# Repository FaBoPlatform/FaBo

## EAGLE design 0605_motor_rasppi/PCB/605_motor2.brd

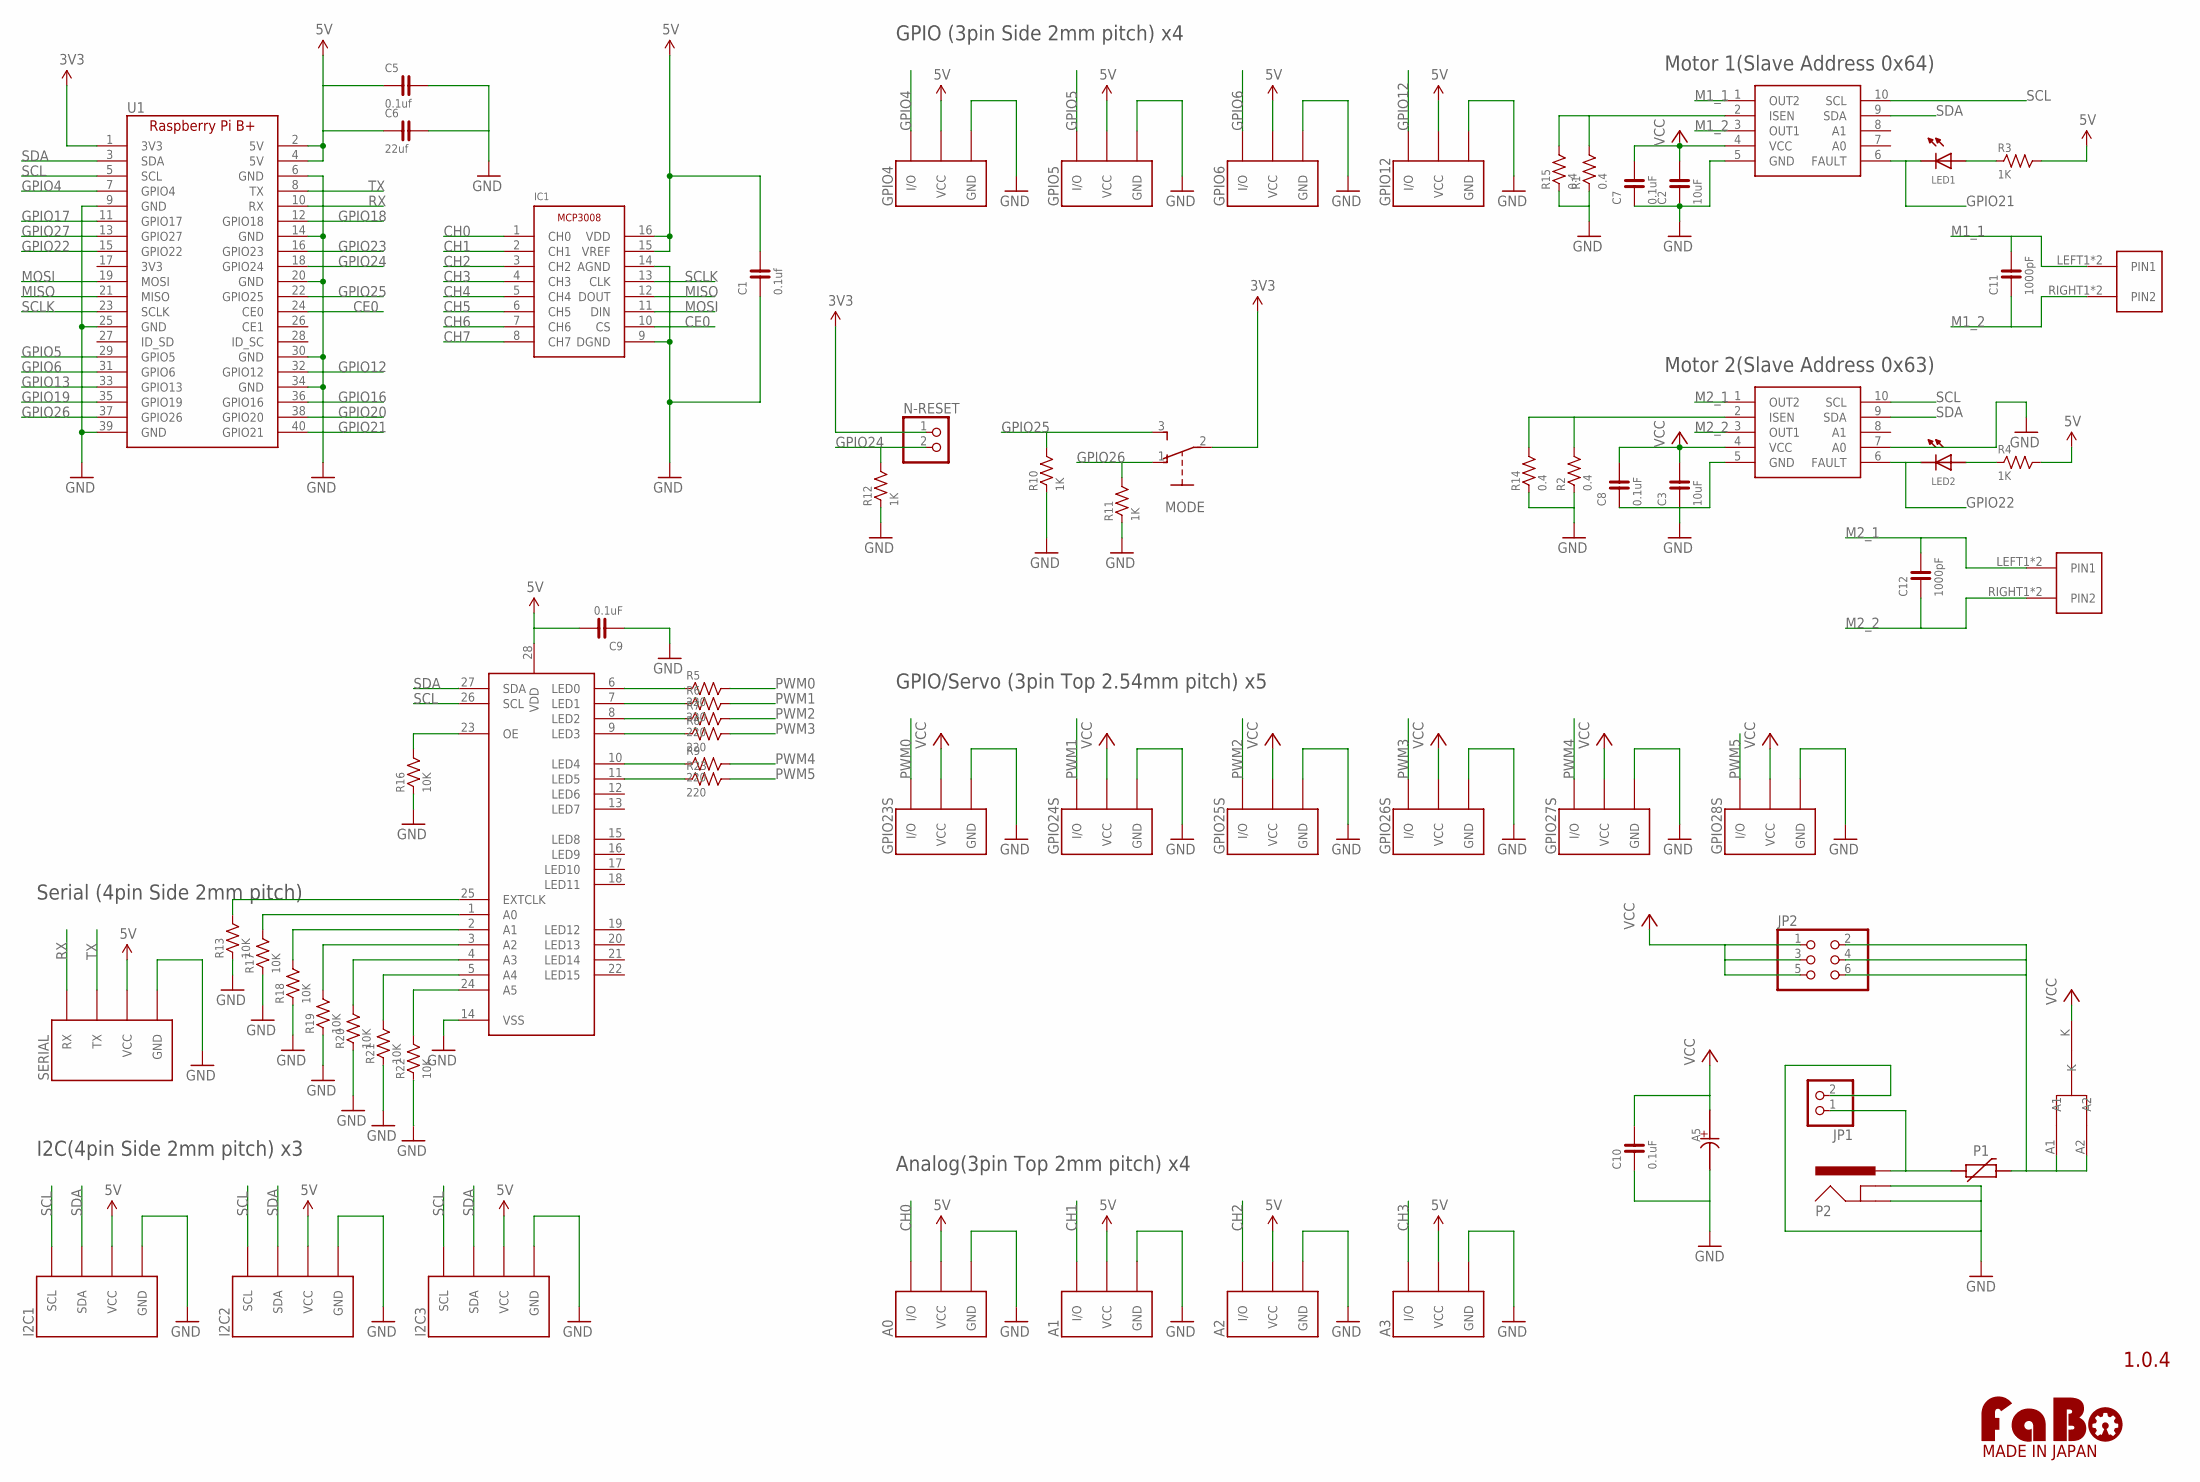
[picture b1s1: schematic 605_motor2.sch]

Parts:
A0, A1, A2, A3: FABO_BRICK_3PIN-B03B-PASK-1; FABO_BRICK_3PIN_B03B-PASK-1
A5: CAPACITOR-ALUMIN_D12_5; D12.5
C1, C5: 0.1uf; 0603
C2, C3: 10uF; 0603
C6: 22uf; 0603
C7, C8, C9, C10: 0.1uF; 0603
C11, C12: 1000pF; 0603
GPIO4, GPIO5, GPIO6, GPIO12: FABO_BRICK_3PIN-S03B-PASK-2; FABO_BRICK_3PIN_S03B-PASK-2
GPIO23S, GPIO24S, GPIO25S, GPIO26S, GPIO27S, GPIO28S: FABO_BRICK_3PIN-HEADER; FABO_BRICK_3PIN_HEADER
I2C1, I2C2, I2C3: FABO_BRICK_I2C-S04B-PASK-2; FABO_BRICK_I2C_S04B-PASK-2
IC1: MICROCHIP-MCP3008
JP1: PINHD-1X2; 1X02
JP2: PINHD-2X3; 2X03
LED1, LED2: LED-0603; 0603
MODE: SLIDE-EG1218; EG1218
N-RESET: PINHD-1X2; 1X02
P1: POLYSWITCH1206; 1206
P2: DC-JACKM04339A0; M04339A0
R1, R2, R14, R15: 0.4; 0603
R3, R4, R10, R11, R12: 1K; 0603
R5, R6, R7, R8, R9, R23: 220; 0603
R13, R22: 10K; 0402
R16, R17, R18, R19, R20, R21: 10K; 0603
S1: STPS15L30C
SERIAL: FABO_BRICK_SERIAL-S04B-PASK-2; FABO_BRICK_SERIAL_S04B-PASK-2
U1: RASPBERRY_PI_B+
U$8, U$10: DRV8830
U$9: PCA9685
U$12, U$13: ML-1400-S1
U$14: LOGO_FABO-M; LOGO_FABO_MS

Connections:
3V3: MODE.2, N-RESET.1, U1.1 (3V3)
5V: A0.VCC, A1.VCC, A2.VCC, A3.VCC, C1.2, C5.1, C6.1, C9.2, GPIO4.VCC, GPIO5.VCC, GPIO6.VCC, GPIO12.VCC, I2C1.VCC, I2C2.VCC, I2C3.VCC, IC1.15 (VREF), IC1.16 (VDD), R3.2, R4.2, SERIAL.VCC, U1.2 (5V), U1.4 (5V), U$9.28 (VDD)
CE0: IC1.10 (CS), U1.24 (CE0)
CH0: A0.I/O, IC1.1 (CH0)
CH1: A1.I/O, IC1.2 (CH1)
CH2: A2.I/O, IC1.3 (CH2)
CH3: A3.I/O, IC1.4 (CH3)
CH4: IC1.5 (CH4)
CH5: IC1.6 (CH5)
CH6: IC1.7 (CH6)
CH7: IC1.8 (CH7)
GND: A0.GND, A1.GND, A2.GND, A3.GND, A5.-, C1.1, C2.1, C3.1, C5.2, C6.2, C7.1, C8.1, C9.1, C10.1, GPIO4.GND, GPIO5.GND, GPIO6.GND, GPIO12.GND, GPIO23S.GND, GPIO24S.GND, GPIO25S.GND, GPIO26S.GND, GPIO27S.GND, GPIO28S.GND, I2C1.GND, I2C2.GND, I2C3.GND, IC1.9 (DGND), IC1.14 (AGND), JP1.2, P2.GND@2 (GND), P2.GND@3 (GNDBREAK), R1.1, R2.1, R10.1, R11.1, R12.1, R13.P$1 (1), R14.1, R15.1, R16.1, R17.1, R18.1, R19.1, R20.1, R21.1, R22.P$1 (1), SERIAL.GND, U1.6 (GND), U1.9 (GND), U1.14 (GND), U1.20 (GND), U1.25 (GND), U1.30 (GND), U1.34 (GND), U1.39 (GND), U$8.5 (GND), U$9.14 (VSS), U$10.5 (GND), U$10.7 (A0)
GPIO4: GPIO4.I/O, U1.7 (GPIO4)
GPIO5: GPIO5.I/O, U1.29 (GPIO5)
GPIO6: GPIO6.I/O, U1.31 (GPIO6)
GPIO12: GPIO12.I/O, U1.32 (GPIO12)
GPIO13: U1.33 (GPIO13)
GPIO16: U1.36 (GPIO16)
GPIO17: U1.11 (GPIO17)
GPIO18: U1.12 (GPIO18)
GPIO19: U1.35 (GPIO19)
GPIO20: U1.38 (GPIO20)
GPIO21: LED1.CATHODE, U1.40 (GPIO21), U$8.6 (FAULT)
GPIO22: LED2.CATHODE, U1.15 (GPIO22), U$10.6 (FAULT)
GPIO23: U1.16 (GPIO23)
GPIO24: N-RESET.2, R12.2, U1.18 (GPIO24)
GPIO25: MODE.3, R10.2, U1.22 (GPIO25)
GPIO26: MODE.1, R11.2, U1.37 (GPIO26)
GPIO27: U1.13 (GPIO27)
LED0: R5.1, U$9.6 (LED0)
LED1: R6.1, U$9.7 (LED1)
LED2: R7.1, U$9.8 (LED2)
LED3: R8.1, U$9.9 (LED3)
LED4: R9.1, U$9.10 (LED4)
LED5: R23.1, U$9.11 (LED5)
M1_1: C11.2, U$8.1 (OUT2), U$12.LEFT1 (PIN1), U$12.LEFT2 (PIN1)
M1_2: C11.1, U$8.3 (OUT1), U$12.RIGHT1 (PIN2), U$12.RIGHT2 (PIN2)
M2_1: C12.2, U$10.1 (OUT2), U$13.LEFT1 (PIN1), U$13.LEFT2 (PIN1)
M2_2: C12.1, U$10.3 (OUT1), U$13.RIGHT1 (PIN2), U$13.RIGHT2 (PIN2)
MISO: IC1.12 (DOUT), U1.21 (MISO)
MOSI: IC1.11 (DIN), U1.19 (MOSI)
unnamed: R1.2, R15.2, U$8.2 (ISEN)
unnamed: R2.2, R14.2, U$10.2 (ISEN)
unnamed: LED1.ANODE, R3.1
unnamed: JP1.1, P1.P$1 (1), P2.VCC (PWR)
unnamed: LED2.ANODE, R4.1
unnamed: R16.2, U$9.23 (OE)
unnamed: R13.P$2 (2), U$9.25 (EXTCLK)
unnamed: R17.2, U$9.1 (A0)
unnamed: R18.2, U$9.2 (A1)
unnamed: R19.2, U$9.3 (A2)
unnamed: R20.2, U$9.4 (A3)
unnamed: R21.2, U$9.5 (A4)
unnamed: R22.P$2 (2), U$9.24 (A5)
unnamed: JP2.2, JP2.4, JP2.6, P1.P$2 (2), S1.A1, S1.A2
PWM0: GPIO23S.I/O, R5.2
PWM1: GPIO24S.I/O, R6.2
PWM2: GPIO25S.I/O, R7.2
PWM3: GPIO26S.I/O, R8.2
PWM4: GPIO27S.I/O, R9.2
PWM5: GPIO28S.I/O, R23.2
RX: SERIAL.RX, U1.10 (RX)
SCL: I2C1.SCL, I2C2.SCL, I2C3.SCL, U1.5 (SCL), U$8.10 (SCL), U$9.26 (SCL), U$10.10 (SCL)
SCLK: IC1.13 (CLK), U1.23 (SCLK)
SDA: I2C1.SDA, I2C2.SDA, I2C3.SDA, U1.3 (SDA), U$8.9 (SDA), U$9.27 (SDA), U$10.9 (SDA)
TX: SERIAL.TX, U1.8 (TX)
VCC: A5.+, C2.2, C3.2, C7.2, C8.2, C10.2, GPIO23S.VCC, GPIO24S.VCC, GPIO25S.VCC, GPIO26S.VCC, GPIO27S.VCC, GPIO28S.VCC, JP2.1, JP2.3, JP2.5, S1.K, U$8.4 (VCC), U$10.4 (VCC)

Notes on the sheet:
1.0.4
GPIO (3pin Side 2mm pitch) x4
I2C(4pin Side 2mm pitch) x3
Serial (4pin Side 2mm pitch)
GPIO/Servo (3pin Top 2.54mm pitch) x5
Analog(3pin Top 2mm pitch) x4
Motor 1(Slave Address 0x64)
Motor 2(Slave Address 0x63)

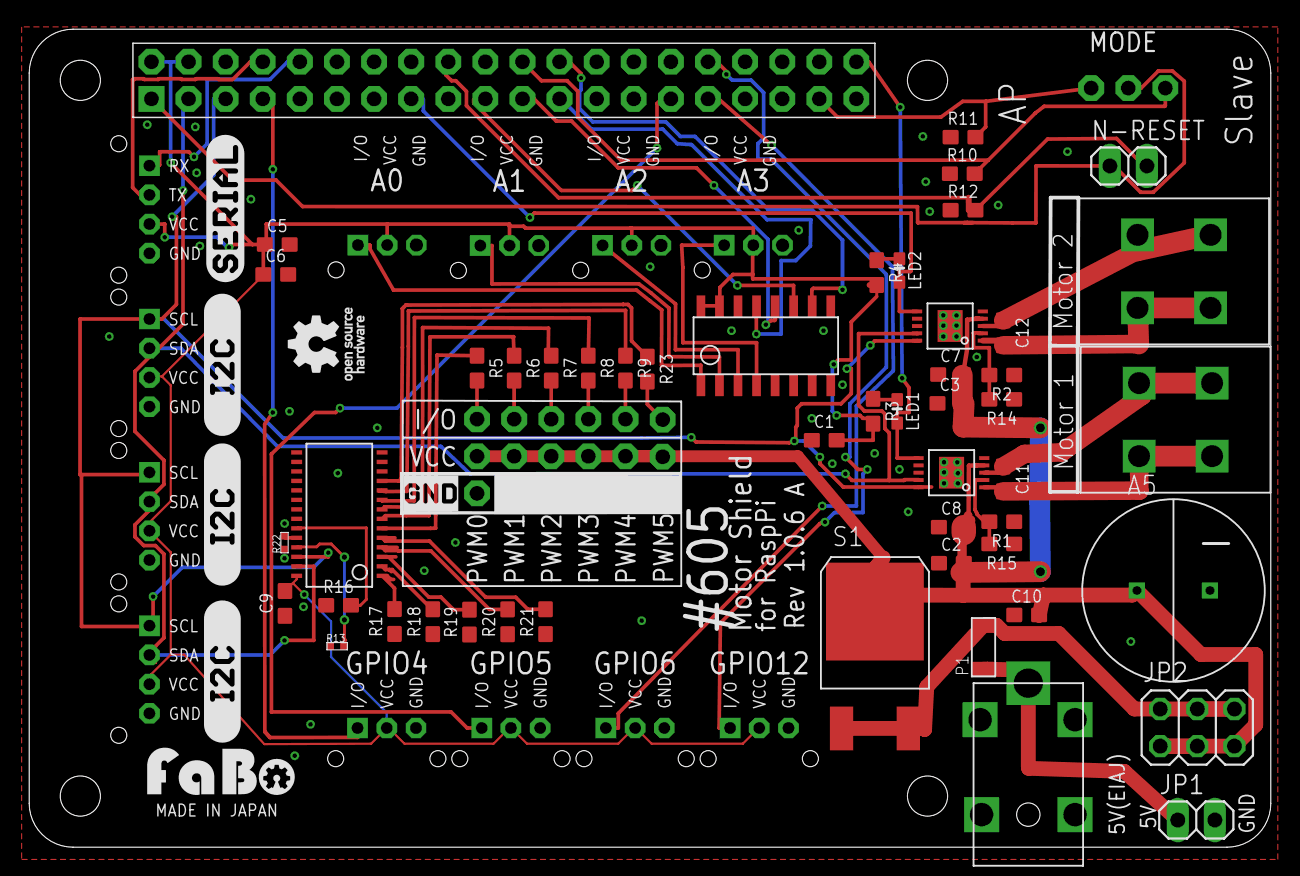
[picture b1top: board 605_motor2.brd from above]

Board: 2 copper layers, 85.0 x 56.0 mm, 76 parts (0 on the bottom side), 55 nets.

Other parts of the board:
U$2, U$5, U$6: LOGO_SILK_I2C
U$3: LOGO_SILK_SERIAL2
U$4: LOGO_OSHW_T_MS
U$7: LOGO_SILK_GND

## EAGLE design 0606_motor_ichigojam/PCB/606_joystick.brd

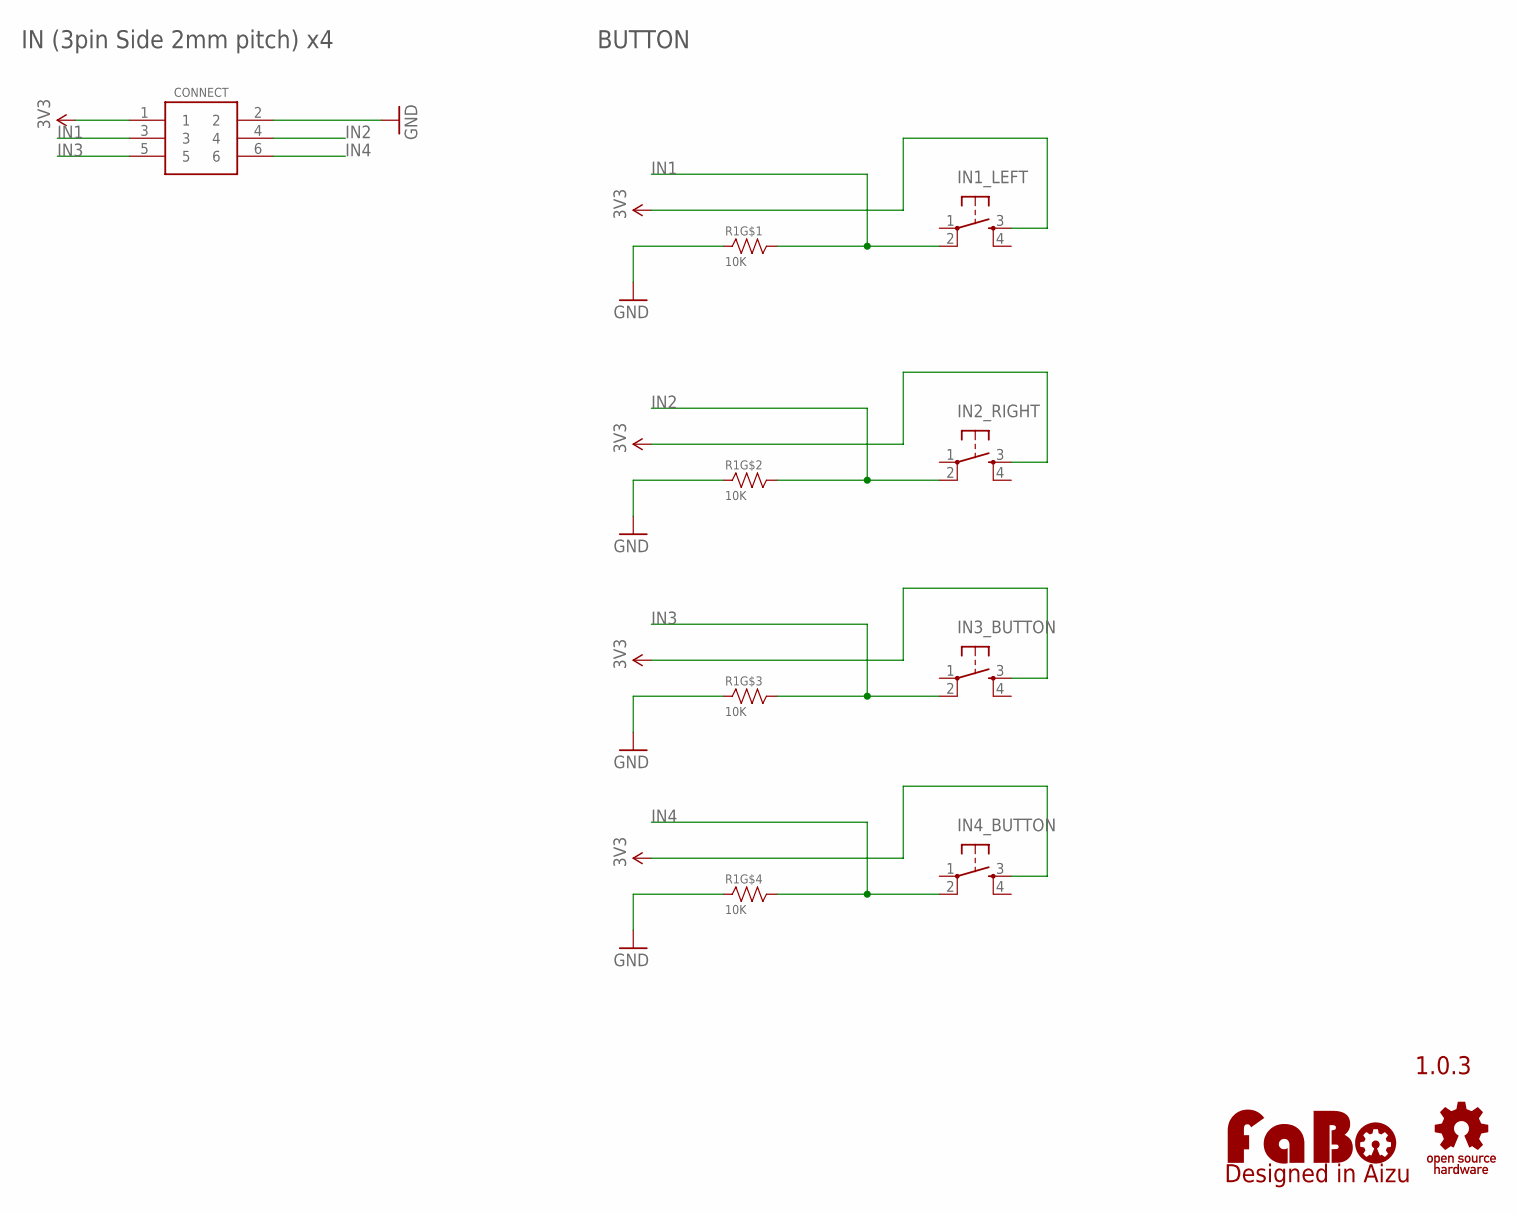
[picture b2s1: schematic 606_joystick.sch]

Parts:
CONNECT: IDC_CONNECTOR_BOTTOM; 2X3_IDC_BOTTOM
IN1_LEFT, IN2_RIGHT, IN3_BUTTON, IN4_BUTTON: TACT-SWITCH-12MM; 1273HA-160G-G
LOGO1: LOGO_FABO-M; LOGO_FABO_M
R1: 10K; EXBV8V
U$2: LOGO_OSHW-M_BOTTOM; LOGO_OSHW_M_BOTTOM

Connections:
3V3: CONNECT.1, IN1_LEFT.3, IN2_RIGHT.3, IN3_BUTTON.3, IN4_BUTTON.3
GND: CONNECT.2, R1.1, R1.2 (1), R1.3 (1), R1.4 (1)
IN1: CONNECT.3, IN1_LEFT.2, R1.8 (2)
IN2: CONNECT.4, IN2_RIGHT.2, R1.7 (2)
IN3: CONNECT.5, IN3_BUTTON.2, R1.6 (2)
IN4: CONNECT.6, IN4_BUTTON.2, R1.5 (2)

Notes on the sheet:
1.0.3
IN (3pin Side 2mm pitch) x4
BUTTON

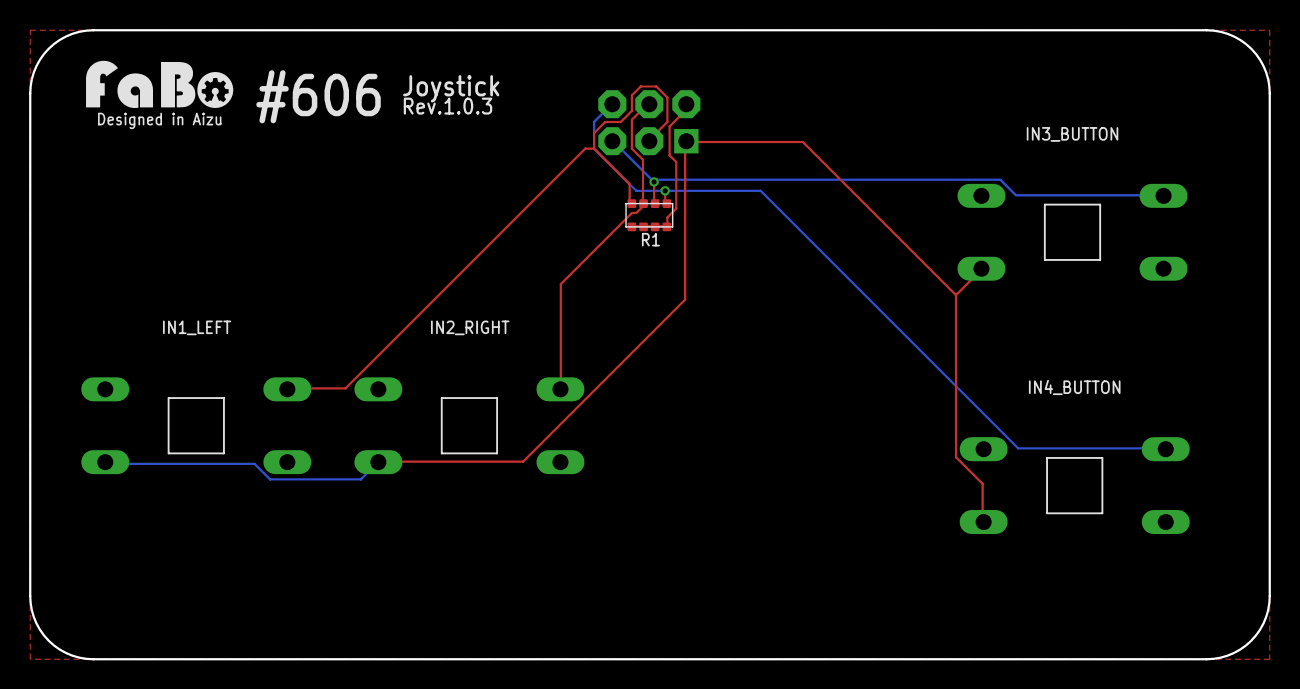
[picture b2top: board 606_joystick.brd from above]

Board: 2 copper layers, 85.1 x 43.2 mm, 8 parts (0 on the bottom side), 6 nets.

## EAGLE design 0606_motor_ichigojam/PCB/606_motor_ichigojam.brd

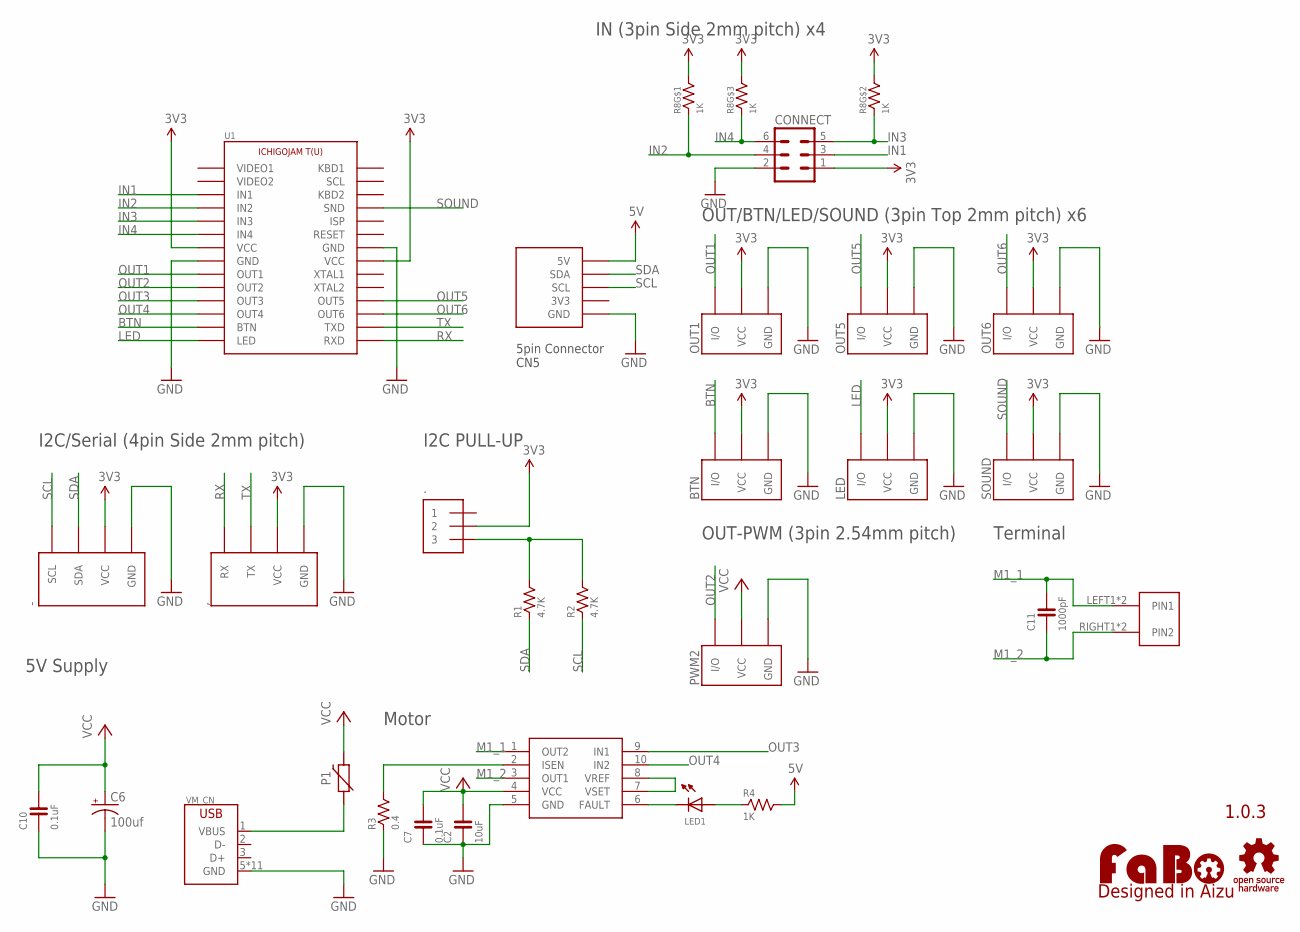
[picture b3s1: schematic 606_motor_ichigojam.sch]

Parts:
,: FABO_BRICK_SERIAL-S04B-PASK-2_LONG; FABO_BRICK_SERIAL_S04B-PASK-2_LONG
-: FABO_BRICK_I2C-S04B-PASK-2_LONG; FABO_BRICK_I2C_S04B-PASK-2_LONG
.: PIN_HEADER_1X3; PIN_1X3
BTN: FABO_BRICK_3PIN-B03B-PASK-1; FABO_BRICK_3PIN_B03B-PASK-1
C2: 10uF; 0603
C6: 100uf; 153CLV-0405
C7, C10: 0.1uF; 0603
C11: 1000pF; 0603
CONNECT: MA03-2
LED: FABO_BRICK_3PIN-B03B-PASK-1; FABO_BRICK_3PIN_B03B-PASK-1
LED1: LED-0603; 0603
LOGO1: LOGO_FABO-M; LOGO_FABO_M
OUT1, OUT5, OUT6: FABO_BRICK_3PIN-B03B-PASK-1; FABO_BRICK_3PIN_B03B-PASK-1
P1: POLYSWITCHMF-NSML1; 1206
PWM2: FABO_BRICK_3PIN-HEADER; FABO_BRICK_3PIN_HEADER
R1, R2: 4.7K; 0603
R3: 0.4; 0603
R4: 1K; 0603
R8: 1K; EXBV8V
SOUND: FABO_BRICK_3PIN-B03B-PASK-1; FABO_BRICK_3PIN_B03B-PASK-1
U1: ICHIGOJAM_T-NOLABEL; ICHIGOJAM_T_NOLABEL
U$2: LOGO_OSHW-M_BOTTOM; LOGO_OSHW_M_BOTTOM
U$6: DRV8832; DRV8830
U$12: ML-1400-S1
VM_CN: USB-ZX62D; ZX62D-B-5PA8

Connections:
3V3: ,.VCC, -.VCC, ..2, BTN.VCC, CONNECT.1, LED.VCC, OUT1.VCC, OUT5.VCC, OUT6.VCC, R8.6 (2), R8.7 (2), R8.8 (2), SOUND.VCC, U1.VCC1 (VCC), U1.VCC2 (VCC)
5V: R4.2, U1.5V
BTN: BTN.I/O, U1.BTN
GND: ,.GND, -.GND, BTN.GND, C2.1, C6.-, C7.1, C10.1, CONNECT.2, LED.GND, OUT1.GND, OUT5.GND, OUT6.GND, PWM2.GND, R3.1, SOUND.GND, U1.GND1 (GND), U1.GND2 (GND), U1.GND3 (GND), U$6.5 (GND), VM_CN.5 (GND), VM_CN.B1 (GND), VM_CN.B2 (GND), VM_CN.B3 (GND), VM_CN.B4 (GND), VM_CN.T1 (GND), VM_CN.T2 (GND), VM_CN.T3 (GND), VM_CN.T4 (GND), VM_CN.T5 (GND), VM_CN.T6 (GND)
GPIO21: LED1.CATHODE, U$6.6 (FAULT)
IN1: CONNECT.3, U1.IN1
IN2: CONNECT.4, R8.1, U1.IN2
IN3: CONNECT.5, R8.2 (1), U1.IN3
IN4: CONNECT.6, R8.3 (1), U1.IN4
LED: LED.I/O, U1.LED
M1_1: C11.2, U$6.1 (OUT2), U$12.LEFT1 (PIN1), U$12.LEFT2 (PIN1)
M1_2: C11.1, U$6.3 (OUT1), U$12.RIGHT1 (PIN2), U$12.RIGHT2 (PIN2)
unnamed: ..3, R1.2, R2.2
unnamed: R3.2, U$6.2 (ISEN)
unnamed: U$6.7 (VSET), U$6.8 (VREF)
unnamed: LED1.ANODE, R4.1
unnamed: P1.P$1 (1), VM_CN.1 (VBUS)
OUT1: OUT1.I/O, U1.OUT1
OUT2: PWM2.I/O, U1.OUT2
OUT3: U1.OUT3, U$6.9 (IN1)
OUT4: U1.OUT4, U$6.10 (IN2)
OUT5: OUT5.I/O, U1.OUT5
OUT6: OUT6.I/O, U1.OUT6
RX: ,.RX, U1.RXD
SCL: -.SCL, R2.1, U1.SCL2 (SCL)
SDA: -.SDA, R1.1, U1.SDA
SOUND: SOUND.I/O, U1.SND
TX: ,.TX, U1.TXD
VCC: C2.2, C6.+, C7.2, C10.2, P1.P$2 (2), PWM2.VCC, U$6.4 (VCC)

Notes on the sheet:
1.0.3
IN (3pin Side 2mm pitch) x4
OUT/BTN/LED/SOUND (3pin Top 2mm pitch) x6
I2C/Serial (4pin Side 2mm pitch)
I2C PULL-UP
5pin Connector CN5
OUT-PWM (3pin 2.54mm pitch)
5V Supply
Motor
Terminal

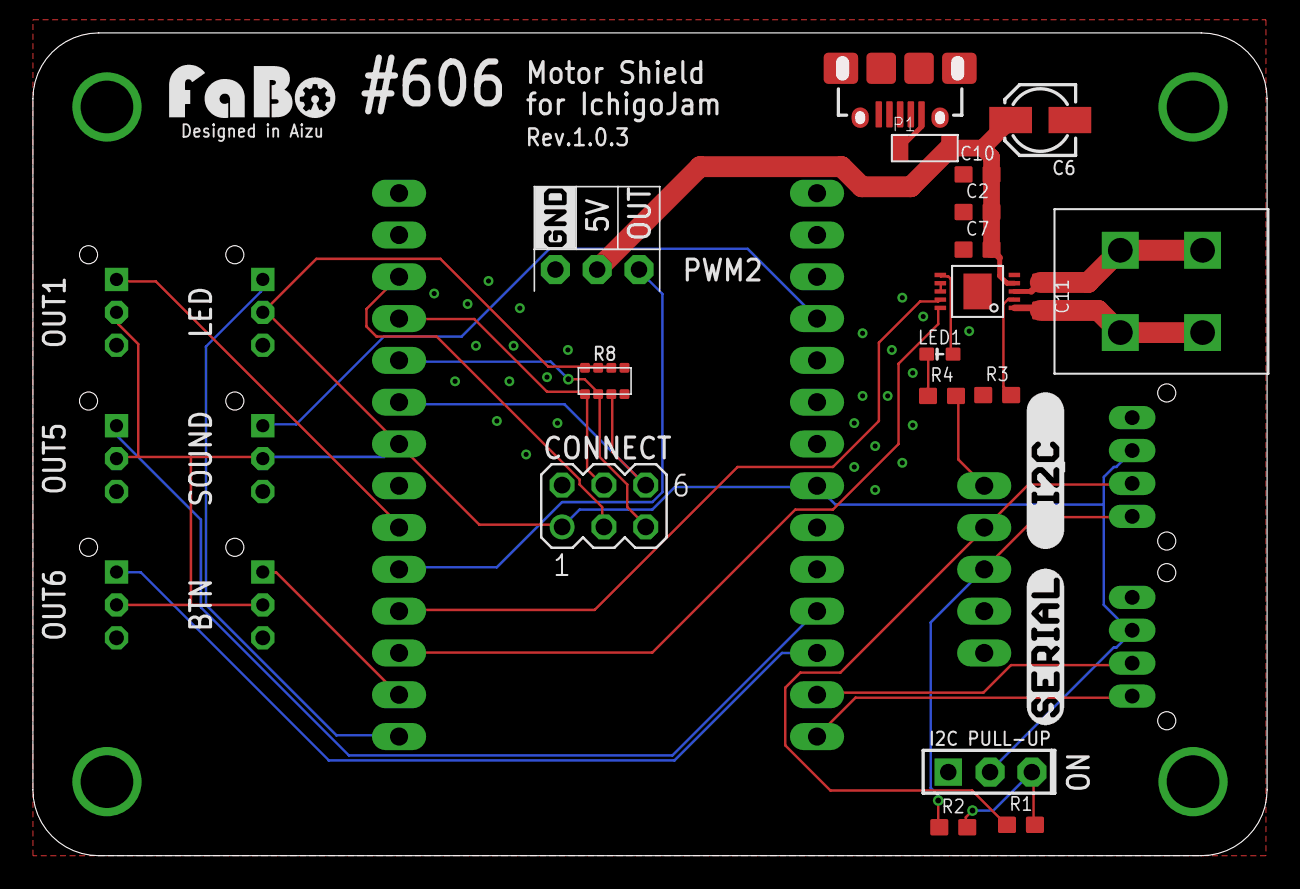
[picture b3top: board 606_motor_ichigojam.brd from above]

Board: 2 copper layers, 75.0 x 50.0 mm, 32 parts (0 on the bottom side), 29 nets.

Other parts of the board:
U$4: LOGO_SILK_SERIAL2
U$5: LOGO_SILK_I2C
U$7: LOGO_SILK_GND

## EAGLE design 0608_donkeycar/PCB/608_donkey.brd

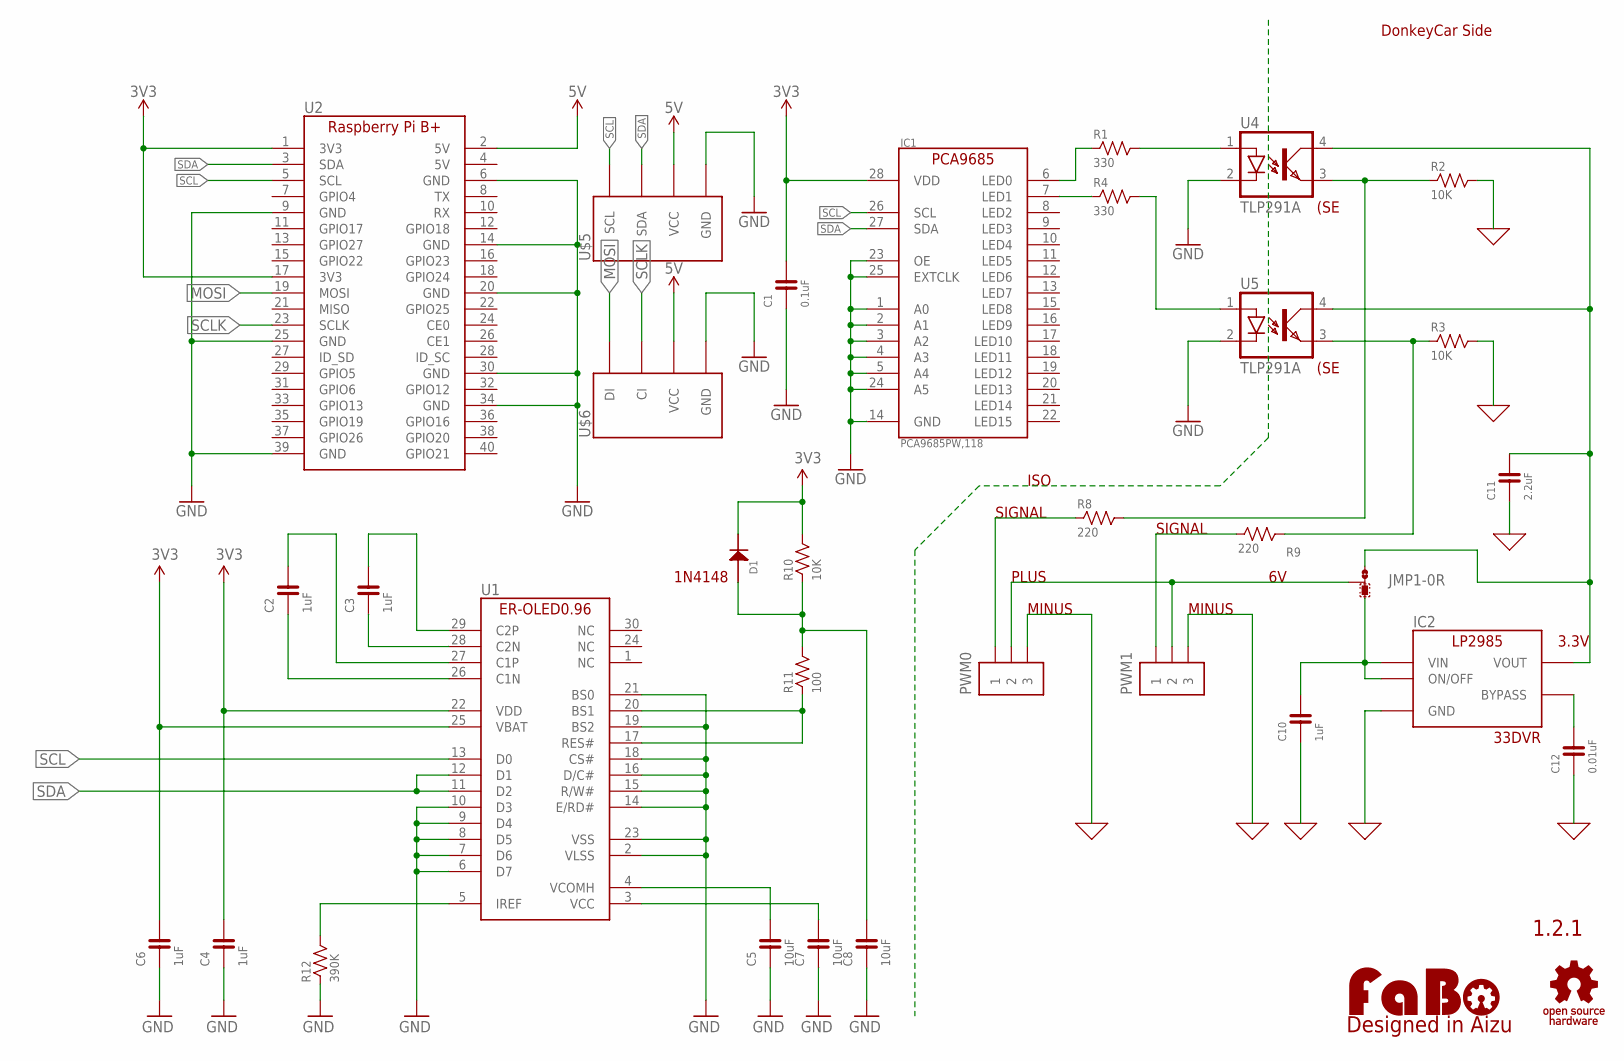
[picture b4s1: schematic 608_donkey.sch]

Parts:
C1: 0.1uF; EIA0603
C2, C3, C4, C6: 1uF; 0603-BOTTOM
C5, C7, C8: 10uF; 0603-BOTTOM
C10: 1uF; EIA0603
C11: 2.2uF; EIA0603
C12: 0.01uF; EIA0603
D1: 1N4148; 1N4148W
IC1: PCA9685PW,118; TSSOP-28
IC2: LP2985-33DBV; SOT-23-5
JMP1: 0R-JUMPB; B0R-JMP
LOGO1: LOGO_FABO-M; LOGO_FABO_M
PWM0, PWM1: PIN_HEADER_1X3; PIN_1X3
R1, R4: 330; 0603-NARROW
R2, R3: 10K; 0603-NARROW
R8, R9: 220; 0603-NARROW
R10: 10K; 0603-BOTTOM
R11: 100; 0603-BOTTOM
R12: 390K; 0603-BOTTOM
U1: ER-OLED0.96-1ER-CON30HT-1; ER-CON30HT-1
U2: RASPBERRY_PI_B+MINI; RASPBERRY_PI_B+_MINI
U4, U5: TLP291A; 11-3C1
U$2: LOGO_OSHW-M_BOTTOM; LOGO_OSHW_M_BOTTOM
U$5: FABO-I2C_BM04B; I2C-BM04B-PASS-1
U$6: FABO-SPI-LED; SPI-BM04B-PASS-1

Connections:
0: C10.1, C11.1, C12.1, IC2.2 (GND), PWM0.3, PWM1.3, R2.2, R3.2
3V3: C1.2, C6.2, D1.CATHODE, IC1.28 (VDD), R10.2, U1.25 (VBAT), U2.1 (3V3), U2.17 (3V3)
5V: U2.2 (5V), U$5.5V (VCC), U$6.5V (VCC)
GND: C1.1, C4.1, C5.1, C6.1, C7.1, C8.1, IC1.1 (A0), IC1.2 (A1), IC1.3 (A2), IC1.4 (A3), IC1.5 (A4), IC1.14 (GND), IC1.23 (OE), IC1.24 (A5), IC1.25 (EXTCLK), R12.1, U1.2 (VLSS), U1.6 (D7), U1.7 (D6), U1.8 (D5), U1.9 (D4), U1.10 (D3), U1.14 (E/RD#), U1.15 (R/W#), U1.16 (D/C#), U1.18 (CS#), U1.19 (BS2), U1.21 (BS0), U1.23 (VSS), U2.6 (GND), U2.9 (GND), U2.14 (GND), U2.20 (GND), U2.25 (GND), U2.30 (GND), U2.34 (GND), U2.39 (GND), U4.2 (C), U5.2 (C), U$5.GND, U$6.GND
MOSI: U2.19 (MOSI), U$6.DI
unnamed: R2.1, R8.2, U4.3 (EMI)
unnamed: R1.2, U4.1 (A)
unnamed: R4.2, U5.1 (A)
unnamed: C11.2, IC2.5 (VOUT), JMP1.3, U4.4 (COL), U5.4 (COL)
unnamed: R3.1, R9.2, U5.3 (EMI)
unnamed: C2.1, U1.26 (C1N)
unnamed: C10.2, IC2.1 (VIN), IC2.3 (ON/OFF), JMP1.1
unnamed: JMP1.2, PWM0.2, PWM1.2
unnamed: C2.2, U1.27 (C1P)
unnamed: C12.2, IC2.4 (BYPASS)
unnamed: PWM0.1, R8.1
unnamed: PWM1.1, R9.1
unnamed: C3.1, U1.28 (C2N)
unnamed: C3.2, U1.29 (C2P)
unnamed: R12.2, U1.5 (IREF)
unnamed: C5.2, U1.4 (VCOMH)
unnamed: C7.2, U1.3 (VCC)
unnamed: R11.1, U1.17 (RES#), U1.20 (BS1)
unnamed: C8.2, D1.ANODE, R10.1, R11.2
unnamed: C4.2, U1.22 (VDD)
PIN_LED0: IC1.6 (LED0), R1.1
PIN_LED1: IC1.7 (LED1), R4.1
SCL: IC1.26 (SCL), U1.13 (D0), U2.5 (SCL), U$5.SCL
SCLK: U2.23 (SCLK), U$6.CI
SDA: IC1.27 (SDA), U1.11 (D2), U1.12 (D1), U2.3 (SDA), U$5.SDA

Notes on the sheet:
1.2.1
ISO
DonkeyCar Side
3.3V
33DVR
PLUS
SIGNAL
MINUS
(SE
1N4148

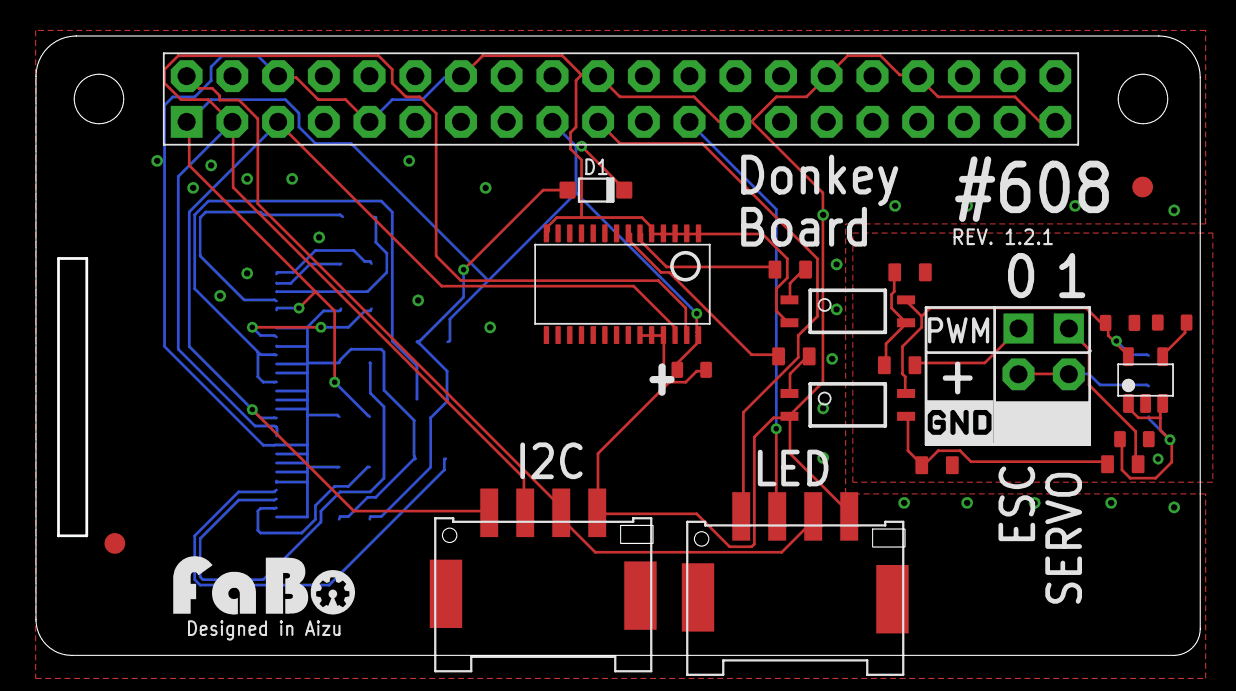
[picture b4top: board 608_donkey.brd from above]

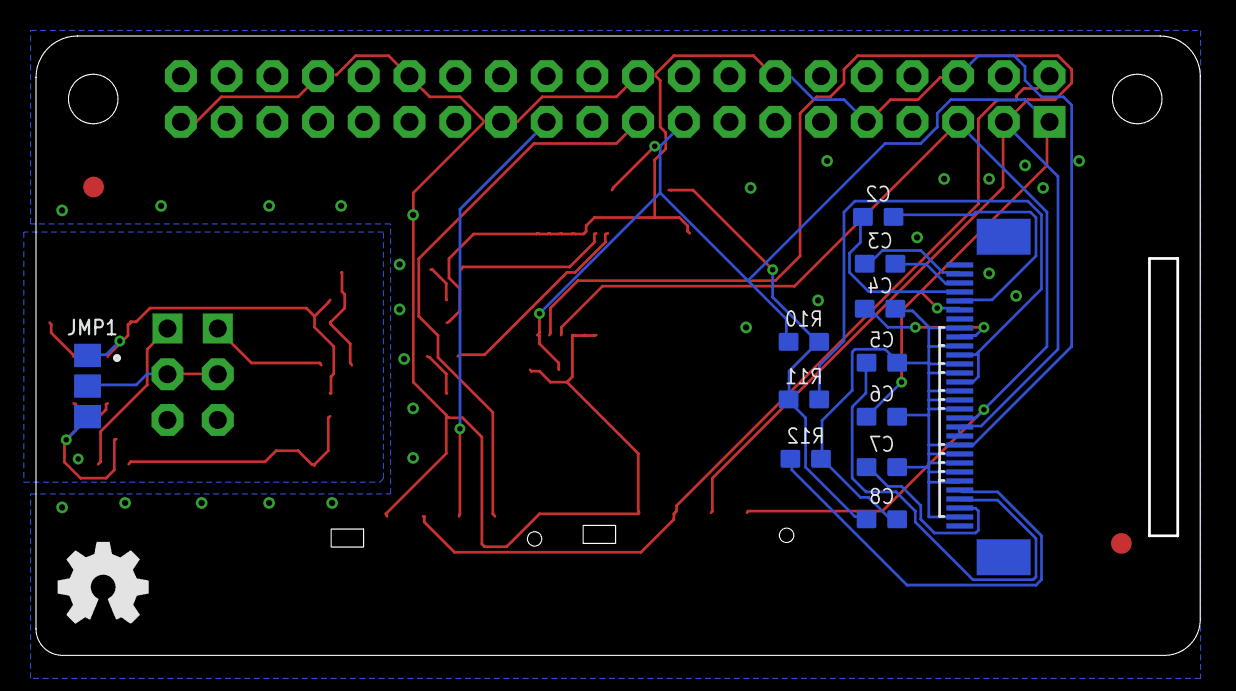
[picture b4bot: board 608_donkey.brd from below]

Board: 2 copper layers, 64.7 x 34.4 mm, 37 parts (2 on the bottom side), 30 nets.

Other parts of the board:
U$3, U$4: MARK_POINT_3MM
U$19: LOGO_SILK_GND

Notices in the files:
parts and their libraries:
FaBo-etc: Released under the Creative Commons Attribution-ShareAlike 4.0 License
https://creativecommons.org/licenses/by-sa/4.0
FaBo-etc: Released under the Creative Commons
